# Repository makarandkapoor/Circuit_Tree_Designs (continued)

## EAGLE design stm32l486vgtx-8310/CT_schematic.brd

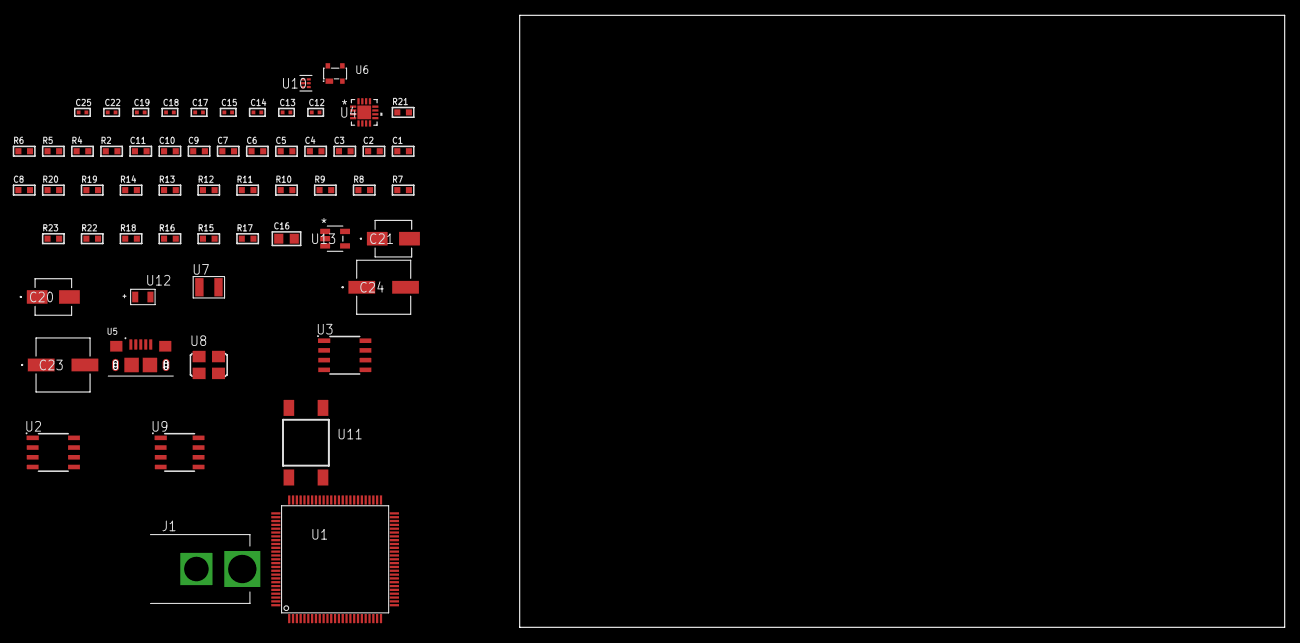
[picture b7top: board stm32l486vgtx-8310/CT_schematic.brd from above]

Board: 2 copper layers, 153.1 x 80.0 mm, 60 parts (0 on the bottom side), 35 nets, no tracks yet.

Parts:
C1, C11: 1e-06; C0603
C2, C3, C4, C5, C6, C7, C9: 1e-07; C0603
C8: 4.7e-06; C0603
C10: 1e-08; C0603
C12, C13: 1e-11; C0402
C14, C15, C19, C25: 1e-08; C0402
C16: 4.7e-06; C0805
C17, C18, C22: 1e-07; C0402
C20: 1e-06; EXV-9B
C21: 2.2e-06; EXV-9B
C23, C24: 0.0001; EXV-9H
J1: PJ-037B; PJ-037B_PACKAGE
R2: 1000.0; R0603
R4: 4700.0; R0603
R5, R6: 2200.0; R0603
R7, R8, R9, R10, R11, R12, R13, R14, R19, R20: 10000.0; R0603
R15, R16, R18: 100000.0; R0603
R17: 164658.62; R0603
R21: 9100.0; R0603
R22: 680000.0; R0603
R23: 120000.0; R0603
U1: STM32L486VGT6; LQFP100
U2: AT25010B-SSHL-T; SOIC-8
U3: AT25512N-SH-T; SOIC-8
U4: MMA8451QT; QFN-16
U5: 10118193-0001LF; FCI_10118193-0001LF
U6: prtr5v0u2ax; SOT143B
U7: ABS07-32.768KHZ-7-T
U8: ASFL1-25MHZ-NCS; ASFL1
U9: LP2954AIMX/NOPB; LP2954
U10: TPS3895ADRYR; SON-6
U11: 4-1437565-2; SW_4-1437565-2
U12: Q65110A2395; LGM67K-G1J2-24-Z
U13: nc7sz125m5x; NC7SZ125M5X

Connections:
CLK_CRYSTAL_U1_8: C12.1, U1.8, U7.1
CLK_CRYSTAL_U1_9: C13.1, U1.9, U7.2
CLK_U1_12: U1.12, U8.3
GND: C1.2, C2.2, C3.2, C4.2, C5.2, C6.2, C7.2, C8.2, C9.2, C10.2, C11.2, C12.2, C13.2, C14.2, C15.2, C16.2, C17.2, C18.2, C19.2, C20.2, C21.2, C22.2, C23.2, C24.2, C25.2, J1.2, R2.2, R7.2, R18.2, R21.2, R23.2, U1.10, U1.19, U1.20, U1.27, U1.49, U1.74, U1.99, U2.4, U3.4, U4.5, U4.10, U4.12, U4.17, U5.5, U5.6, U5.7, U5.8, U5.9, U6.1, U8.2, U9.4, U10.2, U12.C, U13.1, U13.3
NET_U1_14: R4.1, U1.14, U13.4
NET_U1_92: R5.1, U1.92, U4.4
NET_U1_93: R6.1, U1.93, U4.6
NET_U1_94: R7.1, U1.94
NET_U1_98: U11.3, U11.4
NET_U2_3: R8.1, U2.3
NET_U2_7: R10.1, U2.7
NET_U3_3: R11.1, U3.3
NET_U3_7: R13.1, U3.7
NET_U4_2: C18.1, U4.2
NET_U4_7: R14.1, U4.7
NET_U9_3: R16.1, U9.3
NET_U9_5: R15.1, U9.5
NET_U9_7: R17.2, R18.1, U9.7
NET_U10_1: R20.1, R21.1, U10.1
NET_U10_3: R22.2, R23.1, U10.3
NET_U10_4: R19.1, U10.4, U13.2
NET_U11_1: R2.1, U11.1, U11.2
PROC_SPI1_MISO: U1.31, U3.2
PROC_SPI1_MOSI: U1.32, U3.5
PROC_SPI1_NSS: R12.1, U1.29, U3.1
PROC_SPI1_SCK: U1.30, U3.6
PROC_SPI2_MISO: U1.17, U2.2
PROC_SPI2_MOSI: U1.18, U2.5
PROC_SPI2_NSS: R9.1, U1.51, U2.1
PROC_SPI2_SCK: U1.47, U2.6
PROC_USB_OTG_FS_DM: U1.70, U5.2, U6.3
PROC_USB_OTG_FS_DP: U1.71, U5.3, U6.2
PROC_USB_OTG_FS_VBUS: U1.68, U5.1, U6.4
VCC_S1_4V9: C20.1, C23.1, C24.1, J1.1, R16.2, U9.8
VCC_TIER1_3V3: C1.1, C2.1, C3.1, C4.1, C5.1, C6.1, C7.1, C8.1, C9.1, C10.1, C11.1, C14.1, C15.1, C16.1, C17.1, C19.1, C21.1, C22.1, C25.1, R4.2, R5.2, R6.2, R8.2, R9.2, R10.2, R11.2, R12.2, R13.2, R14.2, R15.2, R17.1, R19.2, R20.2, R22.1, U1.6, U1.11, U1.21, U1.22, U1.28, U1.50, U1.73, U1.75, U1.100, U2.8, U3.8, U4.1, U4.14, U8.4, U9.1, U10.6, U13.5

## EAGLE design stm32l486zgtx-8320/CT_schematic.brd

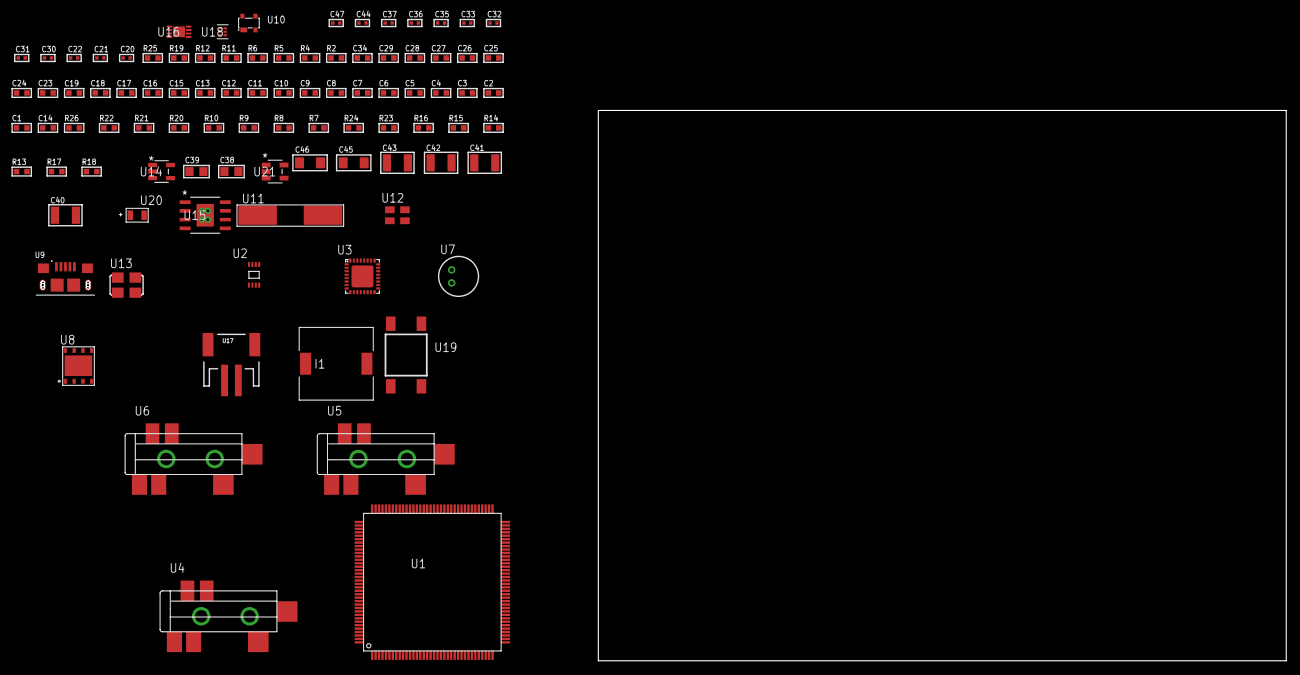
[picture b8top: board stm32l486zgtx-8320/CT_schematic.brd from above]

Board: 2 copper layers, 93 parts (0 on the bottom side), 51 nets, no tracks yet.

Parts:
C1, C19, C23, C24, C25, C26, C27, C28, C29, C34: 1e-06; C0603
C2, C3, C4, C5, C6, C7, C8, C9, C10, C11, C12, C13, C15, C16, C17: 1e-07; C0603
C14: 4.7e-06; C0603
C18: 1e-08; C0603
C20, C21: 1e-11; C0402
C22, C36, C37, C47: 1e-08; C0402
C30, C31, C32, C33, C35, C44: 1e-07; C0402
C38, C39: 1e-05; C0805
C40, C41, C42, C43: 1e-05; C1210
C45, C46: 1e-05; C1206
I1: 3.8e-06; DR1040
R2: 1000.0; R0603
R4: 4700.0; R0603
R5, R6, R19: 2200.0; R0603
R7, R8, R9, R10, R20, R21, R26: 10000.0; R0603
R11, R12: 1270.0; R0603
R13, R14, R15: 100000.0; R0603
R16: 490000.0; R0603
R17: 1000000.0; R0603
R18: 4031.5447154472; R0603
R22: 82000.0; R0603
R23: 300000.0; R0603
R24: 120000.0; R0603
R25: 2000.0; R0603
U1: STM32L486ZGT6; LQFP144
U2: 24AA64T-I/MNY; TDFN-8/6MM
U3: SGTL5000XNAA3; QFN-32
U4, U5, U6: SJ-43515TS-SMT-TR
U7: WM-64PCT; WM-64PC
U8: SST26WF016B-104I/MF; WFDN-8
U9: 10118193-0001LF; FCI_10118193-0001LF
U10: prtr5v0u2ax; SOT143B
U11: ABLS-25.000MHZ-B2F-T
U12: ASEK-32.768KHz-ECST; ASEK
U13: ASFL-24.57MHZ-NCS; ASFL1
U14: ltc3406es5; TSOT-23-5
U15: MIC5234YME; SOIC-8_EP
U16: MCP73831T-2ACI/MC; DFN8_2X3MC
U17: S2B-PH-SM4-TB(LF)(SN); JST-2-SMD
U18: TPS3895ADRYR; SON-6
U19: 4-1437565-2; SW_4-1437565-2
U20: Q65110A2395; LGM67K-G1J2-24-Z
U21: nc7sz125m5x; NC7SZ125M5X

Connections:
CLK_CRYSTAL_U1_23: C20.1, U1.23, U11.1
CLK_CRYSTAL_U1_24: C21.1, U1.24, U11.2
CLK_U1_8: U1.8, U12.3
CLK_U3_21: U3.21, U13.3
GND: C1.2, C2.2, C3.2, C4.2, C5.2, C6.2, C7.2, C8.2, C9.2, C10.2, C11.2, C12.2, C13.2, C14.2, C15.2, C16.2, C17.2, C18.2, C19.2, C20.2, C21.2, C22.2, C30.2, C31.2, C32.2, C33.2, C34.2, C35.2, C36.2, C37.2, C38.2, C39.1, C39.2, C40.2, C41.2, C42.2, C43.2, C44.2, C45.2, C46.2, C47.2, R2.2, R7.2, R8.2, R9.2, R12.2, R16.2, R19.2, R22.2, R24.2, R25.2, U1.16, U1.30, U1.31, U1.38, U1.51, U1.61, U1.71, U1.83, U1.94, U1.107, U1.120, U1.130, U1.143, U2.4, U2.7, U3.1, U3.3, U3.7, U3.EXP, U5.1, U6.1, U7.2, U8.4, U8.9, U9.5, U9.6, U9.7, U9.8, U9.9, U10.1, U12.2, U13.2, U14.2, U15.7, U15.EPAD, U16.6, U16.9, U17.2, U18.2, U20.C, U21.1, U21.3
INPUT_USBPOWER_5V: C45.1, R26.2, U9.1, U10.4, U16.1, U16.2
NET_U1_25: R4.1, U1.25, U21.4
NET_U1_128: R6.1, U1.128, U2.5
NET_U1_129: R5.1, U1.129, U2.6
NET_U1_138: R7.1, U1.138
NET_U1_142: U19.3, U19.4
NET_U2_1: R8.1, U2.1
NET_U2_2: R9.1, U2.2
NET_U2_3: R10.1, U2.3
NET_U3_10: C33.1, U3.10
NET_U3_29: R11.1, U3.29
NET_U3_31: R12.1, U3.31
NET_U4_1: U3.4, U4.1
NET_U4_2: U3.2, U4.2
NET_U4_5: U3.6, U4.5
NET_U5_2: C24.1, U5.2
NET_U5_5: C23.1, U5.5
NET_U6_2: C26.1, C27.1, U6.2
NET_U6_5: C25.1, U6.5
NET_U6_13: C26.2, C27.2
NET_U7_1: C28.1, C29.1, C34.1, U3.16, U7.1
NET_U7_15: C28.2, C29.2
NET_U14_3: I1.1, U14.3
NET_U14_5: R16.1, R17.1, U14.5
NET_U14_ATNET_3: I1.2, R17.2
NET_U15_4: R18.2, R19.1, U15.4
NET_U16_5: R26.1, U16.5
NET_U16_8: R25.1, U16.8
NET_U18_1: R21.1, R22.1, U18.1
NET_U18_3: R23.2, R24.1, U18.3
NET_U18_4: R20.1, U18.4, U21.2
NET_U19_1: R2.1, U19.1, U19.2
PROC_QUADSPI_BK1_IO0: U1.47, U8.5
PROC_QUADSPI_BK1_IO1: U1.46, U8.2
PROC_QUADSPI_BK1_IO2: R14.1, U1.43, U8.3
PROC_QUADSPI_BK1_IO3: R15.1, U1.42, U8.7
PROC_QUADSPI_CLK: U1.63, U8.6
PROC_QUADSPI_NCS: R13.1, U1.64, U8.1
PROC_SAI1_FS_A: U1.3, U3.23
PROC_SAI1_SCK_A: U1.4, U3.24
PROC_SAI1_SD_A: U1.5, U3.26
PROC_USB_OTG_FS_DM: U9.2, U10.3
PROC_USB_OTG_FS_DP: U9.3, U10.2
VCC_S1_3V7: C38.1, C40.1, C41.1, C46.1, U14.4, U15.5, U15.8, U16.3, U16.4, U17.1
VCC_TIER1_1V8: C1.1, C2.1, C3.1, C4.1, C5.1, C6.1, C7.1, C8.1, C9.1, C10.1, C11.1, C12.1, C13.1, C14.1, C15.1, C16.1, C22.1, C30.1, C31.1, C32.1, C35.1, C39.2, C44.1, C47.1, I1.2, R4.2, R5.2, R6.2, R10.2, R11.2, R13.2, R14.2, R15.2, R17.2, R20.2, R21.2, R23.1, U1.6, U1.17, U1.39, U1.52, U1.62, U1.72, U1.84, U1.95, U1.108, U1.121, U1.131, U1.144, U2.8, U3.5, U3.20, U3.30, U8.8, U18.6, U21.5
VCC_TIER1_3V3: C17.1, C18.1, C19.1, C36.1, C37.1, C42.1, C43.1, R18.1, U1.32, U1.33, U1.106, U12.4, U13.4, U15.1
